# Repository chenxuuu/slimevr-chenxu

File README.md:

# slimevr-chenxu
ESP32C3+LSM6DSR方案

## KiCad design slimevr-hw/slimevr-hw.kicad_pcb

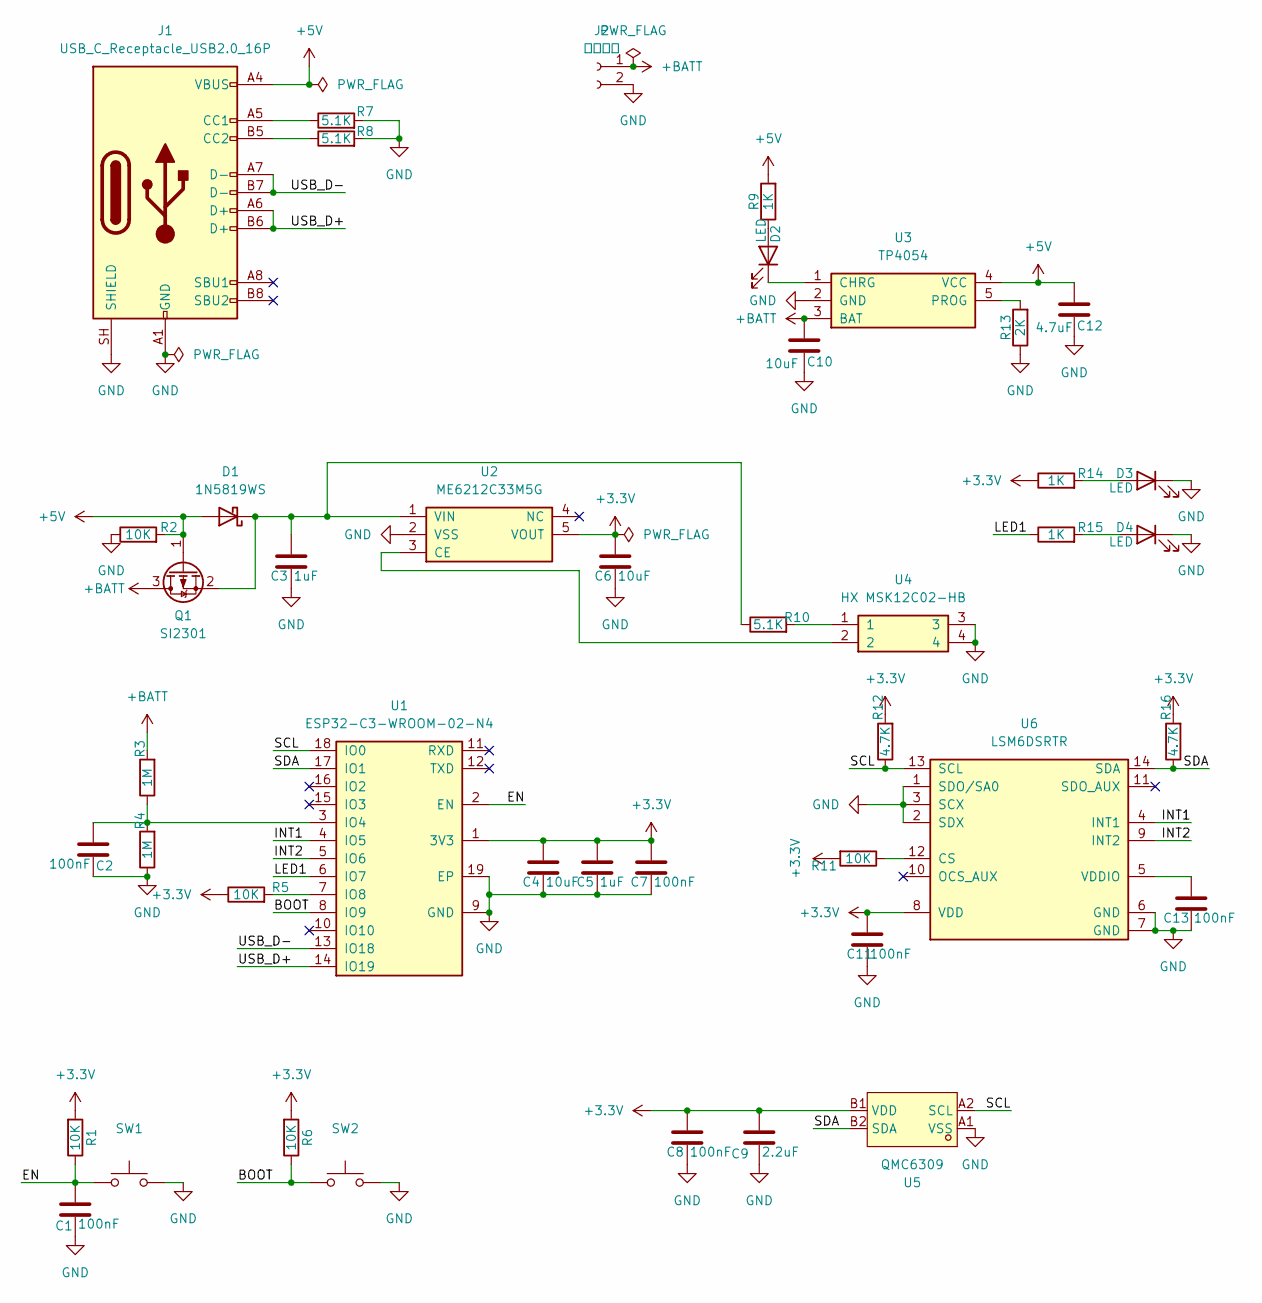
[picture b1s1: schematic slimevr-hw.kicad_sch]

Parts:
C1, C2, C7, C8, C11, C13: 100nF; C_0402_1005Metric
C3, C5: 1uF; C_0603_1608Metric
C4, C6, C10: 10uF; C_0603_1608Metric
C9: 2.2uF; C_0603_1608Metric
C12: 4.7uF; C_0603_1608Metric
D1: 1N5819WS; D_SOD-323
D2, D3, D4: LED; LED_0603_1608Metric
J1: USB_C_Receptacle_USB2.0_16P; USB_C_Receptacle_GCT_USB4105-xx-A_16P_TopMnt_Horizontal
J2: 电池接口; Hirose_DF13-02P-1.25DSA_1x02_P1.25mm_Vertical
Q1: SI2301; MPN SI2301
R1, R2, R5, R6, R11: 10K; R_0402_1005Metric
R3, R4: 1M; R_0402_1005Metric
R7, R8, R10: 5.1K; R_0402_1005Metric
R9, R14, R15: 1K; R_0402_1005Metric
R12, R16: 4.7K; R_0402_1005Metric
R13: 2K; R_0402_1005Metric
SW1, SW2: TS-1088-AR02016; voltage_rating 12 V; MPN TS-1088-AR02016
U1: ESP32-C3-WROOM-02-N4; ESP-WROOM-02-N4; MPN ESP32-C3-WROOM-02-N4
U2: ME6212C33M5G; voltage 6 V; MPN ME6212C33M5G
U3: TP4054; MPN TP4054
U4: HX MSK12C02-HB; MPN HX MSK12C02-HB
U5: QMC6309; X1-WLB0808-4_L0.8-W0.8-P0.40-TL; LCSC Part C5439871
U6: LSM6DSRTR; MPN LSM6DSRTR

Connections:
+3.3V: C4.1, C5.1, C6.1, C7.1, C8.1, C9.1, C11.1, R1.2, R5.1, R6.2, R11.2, R12.2, R14.1, R16.2, U1.1 (3V3), U2.5 (VOUT), U5.B1 (VDD), U6.8 (VDD)
+5V: C12.1, D1.2 (A), J1.A4 (VBUS), J1.A9 (VBUS), J1.B4 (VBUS), J1.B9 (VBUS), Q1.1 (G), R2.2, R9.2, U3.4 (VCC)
+BATT: C10.1, J2.1, Q1.3 (D), R3.2, U3.3 (BAT)
/BOOT: R6.1, SW2.1, U1.8 (IO9)
/EN: C1.1, R1.1, SW1.1, U1.2 (EN)
/INT1: U1.4 (IO5), U6.4 (INT1)
/INT2: U1.5 (IO6), U6.9 (INT2)
/LED1: R15.1, U1.6 (IO7)
/SCL: R12.1, U1.18 (IO0), U5.A2 (SCL), U6.13 (SCL)
/SDA: R16.1, U1.17 (IO1), U5.B2 (SDA), U6.14 (SDA)
/USB_D+: J1.A6 (D+), J1.B6 (D+), U1.14 (IO19)
/USB_D-: J1.A7 (D-), J1.B7 (D-), U1.13 (IO18)
GND: C1.2, C2.2, C3.2, C4.2, C5.2, C6.2, C7.2, C8.2, C9.2, C10.2, C11.2, C12.2, C13.2, D3.1 (K), D4.1 (K), J1.A1 (GND), J1.A12 (GND), J1.B1 (GND), J1.B12 (GND), J1.SH (SHIELD), J2.2, R2.1, R4.1, R7.2, R8.2, R13.1, SW1.2, SW2.2, U1.9 (GND), U1.19 (EP), U2.2 (VSS), U3.2 (GND), U4.3, U4.4, U5.A1 (VSS), U6.1 (SDO/SA0), U6.2 (SDX), U6.3 (SCX), U6.6 (GND), U6.7 (GND)
unnamed: C3.1, D1.1 (K), Q1.2 (S), R10.1, U2.1 (VIN)
unnamed: D2.2 (A), R9.1
unnamed: D2.1 (K), U3.1 (CHRG)
unnamed: D3.2 (A), R14.2
unnamed: D4.2 (A), R15.2
unnamed: J1.A5 (CC1), R7.1
unnamed: J1.B5 (CC2), R8.1
unnamed: R10.2, U4.1
unnamed: C2.1, R3.1, R4.2, U1.3 (IO4)
unnamed: R5.2, U1.7 (IO8)
unnamed: U2.3 (CE), U4.2
unnamed: R13.2, U3.5 (PROG)
unnamed: R11.1, U6.12 (CS)
unnamed: C13.1, U6.5 (VDDIO)

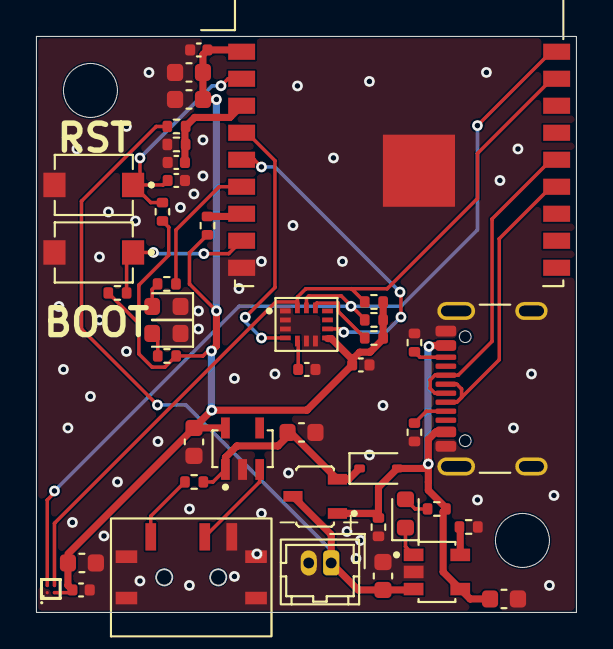
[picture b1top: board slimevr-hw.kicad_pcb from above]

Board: 2 copper layers, 30.0 x 32.0 mm, 44 parts (0 on the bottom side), 27 nets.

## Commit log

2026-04-02 add: 原理图
2026-04-03 update: 改改不合理的地方
2026-04-08 add: 软件固件
2026-04-08 update: 充电方案换更简单的
2026-04-09 update: layout完成
2026-04-13 update: 同步更改
